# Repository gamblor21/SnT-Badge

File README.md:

# As Seen on Show & Tell Badge

This is a PCB badge based on the Adafruit sticker that (pre-covid) would be sent to community members who appeared on their Show and Tell show.

The badge is in the shape and style of the original sticker and made in the FeatherWing format with duel header rows (though single could likely fit).

The front has 6 Neopixels (connected to D5) and a light sensor (hooked to A0). The back has an IMU the ICM-20602 (ICM-20608-G can be used as a drop-in replacement). The IMU is hooked up via I2C.

The source folder has sample code and a basic CircuitPython driver for the ICM-20602 but is far from a full implementation.

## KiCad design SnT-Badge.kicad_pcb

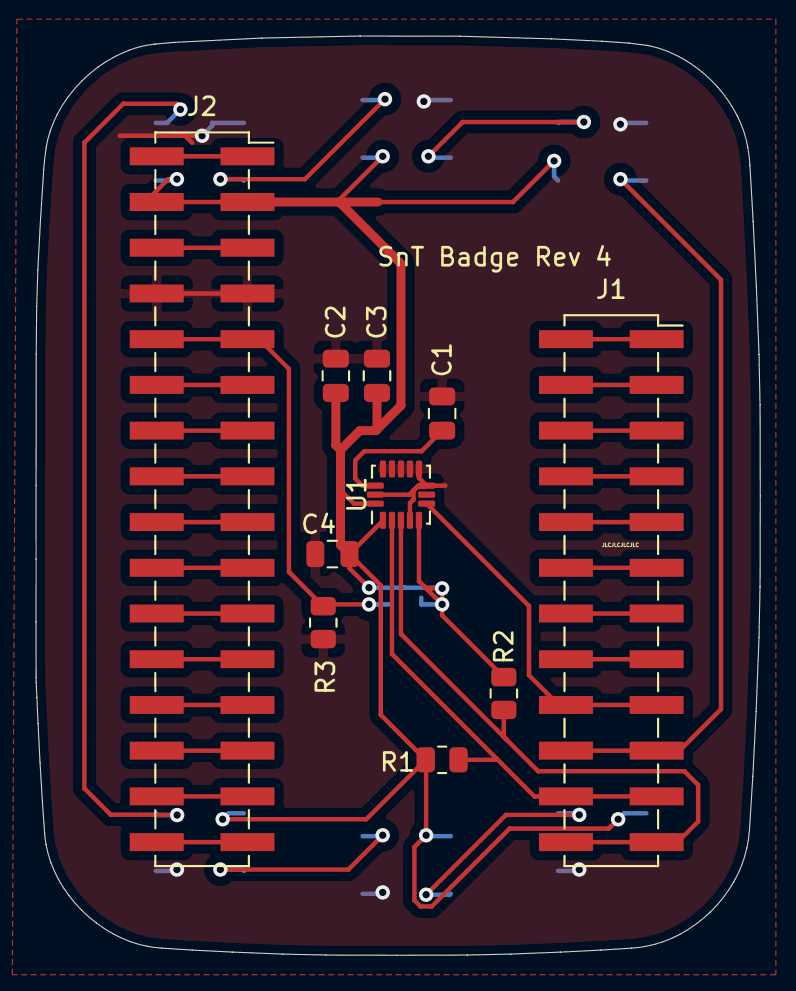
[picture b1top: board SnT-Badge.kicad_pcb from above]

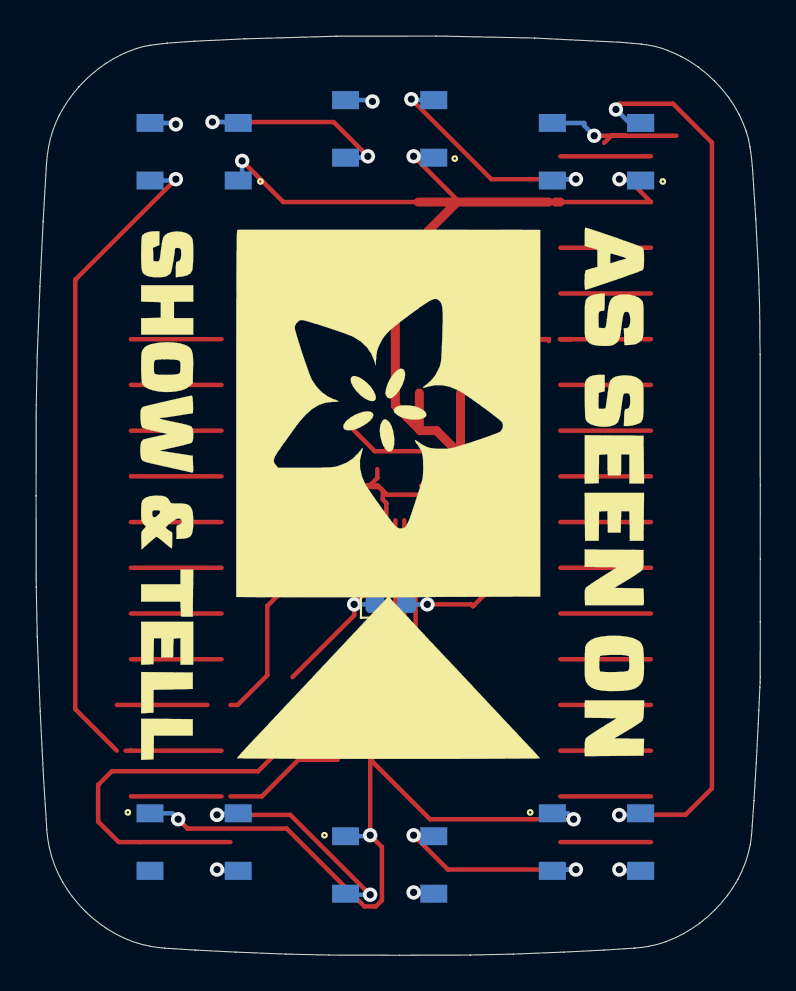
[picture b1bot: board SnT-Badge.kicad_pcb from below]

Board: 2 copper layers, 40.2 x 51.1 mm, 17 parts (7 on the bottom side), 34 nets.

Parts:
C1, C2: 0.1uF; C_0805_2012Metric
C3: 2.2uF; C_0805_2012Metric
C4: 10nF; C_0805_2012Metric
D1: SK6812; LED_SK6812_PLCC4_5.0x5.0mm_P3.2mm
D2, D3, D4, D5, D6: WS2812B; LED_WS2812B_PLCC4_5.0x5.0mm_P3.2mm
D7: D_Photo; D_0603_1608Metric_Pad1.05x0.95mm_HandSolder
J1: Conn_02x12_Row_Letter_Last; PinSocket_2x12_P2.54mm_Vertical_SMD
J2: Conn_02x16_Row_Letter_Last; PinSocket_2x16_P2.54mm_Vertical_SMD
R1, R2, R3: 10k; R_0805_2012Metric
U1: ICM-20602; LGA-16_3x3mm_P0.5mm_LayoutBorder3x5y

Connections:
3VDC: C2.1, C3.1, C4.1, D1.3, D2.1, D3.1, D4.1, D5.1, D6.1, D7.1, J2.3, J2.4, R1.2, R2.2, U1.1, U1.5, U1.16
GND: C1.2, C2.2, C3.2, C4.2, D1.1, D2.3, D3.3, D4.3, D5.3, D6.3, J2.7, J2.8, R3.1, U1.4, U1.8, U1.9, U1.10, U1.11, U1.12, U1.13, U1.15
INT: J1.17, J1.18, U1.6
LEDs: D1.2, J1.19, J1.20
LIGHT: D7.2, J2.9, J2.10, R3.2
unnamed: D1.4, D2.4
unnamed: D2.2, D3.4
unnamed: D3.2, D4.4
unnamed: D4.2, D5.4
unnamed: D5.2, D6.4
unnamed: J1.1, J1.2
unnamed: J1.3, J1.4
unnamed: J1.5, J1.6
unnamed: J1.7, J1.8
unnamed: J1.9, J1.10
unnamed: J1.11, J1.12
unnamed: J1.13, J1.14
unnamed: J1.15, J1.16
unnamed: J2.1, J2.2
unnamed: J2.5, J2.6
unnamed: J2.11, J2.12
unnamed: J2.13, J2.14
unnamed: J2.15, J2.16
unnamed: J2.17, J2.18
unnamed: J2.19, J2.20
unnamed: J2.21, J2.22
unnamed: J2.23, J2.24
unnamed: J2.25, J2.26
unnamed: J2.27, J2.28
unnamed: J2.29, J2.30
unnamed: J2.31, J2.32
REGOUT: C1.1, U1.14
SCL: J1.21, J1.22, R1.1, U1.2
SDA: J1.23, J1.24, R2.1, U1.3

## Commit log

2021-05-23 Adding source
2021-05-23 Adding ICM20602 driver
2021-05-30 Added front and back images of finished board
2021-05-30 Added BOM
2021-05-30 Update and rename LICENSE to Software-LICENSE
2021-05-30 Create hardware-LICENSE
2021-05-31 adding_documentation
2021-06-03 Add oshw facts image
